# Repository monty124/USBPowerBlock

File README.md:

# USBPowerBlock
Tasmota controlled USB Switching

# Why?

So many things are usb powered but can not or are not able to be integrated easily within Home Assistant; or programable.

Want to turn something on or off automatically? you will need to buy [something else](https://www.aliexpress.com/w/wholesale-TZT-sinilink-USB.html?spm=a2g0o.productlist.search.0)! and it still needs a power source

Want it to be integrated into [Home Assistant](https://www.home-assistant.io/) and or control its [privacy](https://www.voanews.com/a/east-asia-pacific_voa-news-china_cybersecurity-experts-worried-chinese-firms-control-smart-devices/6209815.html)? good luck off the shelf, you may need to [flash it](https://templates.blakadder.com/sinilink_XY-WFUSB.html) (if its supported)

Want more than one device powered from a single power source, you will need a powered hub and multiple other devices, or multiple power sources, this effectively combines 5 [sinilinks'](https://www.aliexpress.com/w/wholesale-TZT-sinilink-USB.html?spm=a2g0o.productlist.search.0) into a single unit.

It has been designed to power a device up to 500mA with the listed BOM, but is flexible (see Options below)

500mA was chosen as a default, as a 5v 2.5A/3A powesupply is very common and affordable (you probably already have one!) and this was intended to switch very low current devices (think, lights, IoT devices, etc)

For more information on USB power draw:

https://en.wikipedia.org/wiki/USB_hardware#Allowable_current_draw

Note, this does not identify itself as a PD or Battery Charging (BC) Device! (yet), technically each port should be limited to 100mA in its current design, but taking some liberties here!

# BOM

[Bill Of Materials](./USBPowerBlock_BOM.csv)

|Reference            |Value                    |Datasheet                                                                                                              |Qty                                                      |Product_Link|
|---------------------|-------------------------|-----------------------------------------------------------------------------------------------------------------------|---------------------------------------------------------|------------|
|C1,C3,C4,C6          |0.1UF-0805-25V-_+80_-20%_|https://www.lcsc.com/datasheet/lcsc_datasheet_2304140030_TORCH-CT41G-0805-2X1-50V-0-1-F-K-N_C126469.pdf                |4                                                        |https://www.lcsc.com/product-detail/C126469.html|
|C2,C5                |10UF-0805-16V-10%        |https://www.lcsc.com/datasheet/lcsc_datasheet_2409292003_Vishay-Intertech-VJ0805G106KXYTW1BC_C5334346.pdf              |2                                                        |https://www.lcsc.com/product-detail/C5334346.html|
|D1 |Blue |https://wmsc.lcsc.com/wmsc/upload/file/pdf/v2/lcsc/2208221800_TCWIN-TC0805GF01-1CSA_C5137315.pdf|1  |https://lcsc.com/product-detail/C5137315.html|
|D2 |Green|https://wmsc.lcsc.com/wmsc/upload/file/pdf/v2/lcsc/2410121920_Lite-On-LTST-C170KGKT_C98221.pdf  |1  |https://lcsc.com/product-detail/C5137315.html|
|D3 |Red  |https://wmsc.lcsc.com/wmsc/upload/file/pdf/v2/lcsc/2504101957_XINGLIGHT-XL-2012SURC_C965812.pdf |1  |https://lcsc.com/product-detail/C5137315.html|
|F1,F2,F3,F4,F5       |JK-SMD0805-020-30V       |https://www.lcsc.com/datasheet/lcsc_datasheet_2007081813_Jinrui-Electronic-Materials-Co--JK-SMD0805-020-30V_C516070.pdf|5                                                        |https://www.lcsc.com/product-detail/C516070.html|
|J1,J2,J3,J4,J5       |USB_A                    | Vertical USB-A                                                                                                                      |5                                                        |https://www.aliexpress.com/item/1005005865561469.html or https://www.lcsc.com/product-detail/C456015.html|
|J6 |IO   |~                                         |1  |~                                                    |
|J7                   |Power_In                 | XH2.5                                                                                                                      |1                                                        |https://www.aliexpress.com/item/1005003137518807.html|
|Q1,Q2,Q3,Q4,Q5       |LMAK15N10                |https://www.lcsc.com/datasheet/lcsc_datasheet_2504180925_VBsemi-Elec-ME15N10-VB_C710010.pdf                            |5                                                        |https://www.lcsc.com/product-detail/C710010.html|
|R1,R3,R4,R5,R7,R9,R11,R15,R16|10KOHM-0805-1_10W-1%     |https://www.lcsc.com/datasheet/lcsc_datasheet_2410121912_TyoHM-RMC080510K5-N_C269724.pdf                               |9                                                        |https://www.lcsc.com/product-detail/C269724.html|
|R2,R6,R8,R10,R12     |100R                     |https://www.lcsc.com/datasheet/lcsc_datasheet_2411221126_UNI-ROYAL-Uniroyal-Elec-0805W8F1000T5E_C17408.pdf             |5                                                        |https://www.lcsc.com/product-detail/C17408.html|
|R13,R17|68OHM-0805-1_10W-1%|https://www.lcsc.com/datasheet/lcsc_datasheet_2410121912_TyoHM-RMC080510K5-N_C269724.pdf|2  |https://www.lcsc.com/product-detail/C269724.html|
|R14    |470OHM-0805-1_10W-1%|https://www.lcsc.com/datasheet/lcsc_datasheet_2410121912_TyoHM-RMC080510K5-N_C269724.pdf|1  |https://www.lcsc.com/product-detail/C269724.html|
|U1                   |ESP-WROOM-02             |https://www.espressif.com/sites/default/files/documentation/0c-esp-wroom-02_datasheet_en.pdf                           |1                                                        |https://www.lcsc.com/product-detail/C529584.html|
|U2                   |AMS1117-3.3              |http://www.advanced-monolithic.com/pdf/ds1117.pdf                                                                      |1                                                        |https://www.lcsc.com/product-detail/C2992570.html|

Misc Components:

| Product | Example Link | Qty |
| ------- | -------------| --- |
| 5V 2.5A (min) Power Supply | https://www.wagneronline.com.au/5-volt-3a-switch-mode/power-supplies/power-lighting/smp5v-3a-21r-35234/10297/pd/ | 1 |
| Power Socket 5.5x2.1mm| https://www.aliexpress.com/item/1005002601060281.html | 1 |
| Hook Up Wire ~24AWG | https://www.aliexpress.com/item/1005007278251470.html | 1x Length Red <br> 1x Length Black |
| PCB | [Here](./USBPowerBlock/gerber) | 1 |
| Case | [Here](./Case) | 1 |
| Flexy Pins | https://core-electronics.com.au/flexypin-pack-of-100.html | 18 |

# Options

## I want more current! 

- Swap out your power adaptor for something that can supply your desired current along with approx (at least) ~250mA for the ESP
- Replace F1-F5 with a suitable current rating; 0805 package self healing fuse

  - https://www.lcsc.com/product-detail/C516070.html 500mA
  - https://www.lcsc.com/product-detail/C369151.html 1.5A
  - https://www.lcsc.com/product-detail/C2830234.html 2.2A
  
The MOSFETS are rated to approx 15A each, which is overkill.

## I don't need switched outputs but want like 5 powered USB ports

- leave all components out except J1-J5 + J7
- leave F1-F5 in (and up-rate the fuse value, see above) or replace with 0805 0 Ohm links (https://www.lcsc.com/product-detail/C96345.html)
- solder JP1-JP5
- ensure your power adaptor has enough current

# PCB

Gerber files are available to have printed

- https://www.pcbway.com/
- https://jlcpcb.com/

# 3D Printed Case

STL's are available in this repo to print or have printed

- https://www.pcbway.com/rapid-prototyping/manufacture/?type=2
- https://jlc3dp.com/?source=JLCPCB-top-productbar

# Assembly

TBC

# Tasmota

TBC

# What Next?

Some notes on desired features! (maybe, but probably not)

- Power from a 12V supply?
- Increased power outputs and PD/BC support?
- Compliant USB-C PD Power Source 
- Completed photos
- Flexypin-less design?
- ESP32-C3-WROOM design (ESP-WROOM-02 is EOL) with and without FlexyPin

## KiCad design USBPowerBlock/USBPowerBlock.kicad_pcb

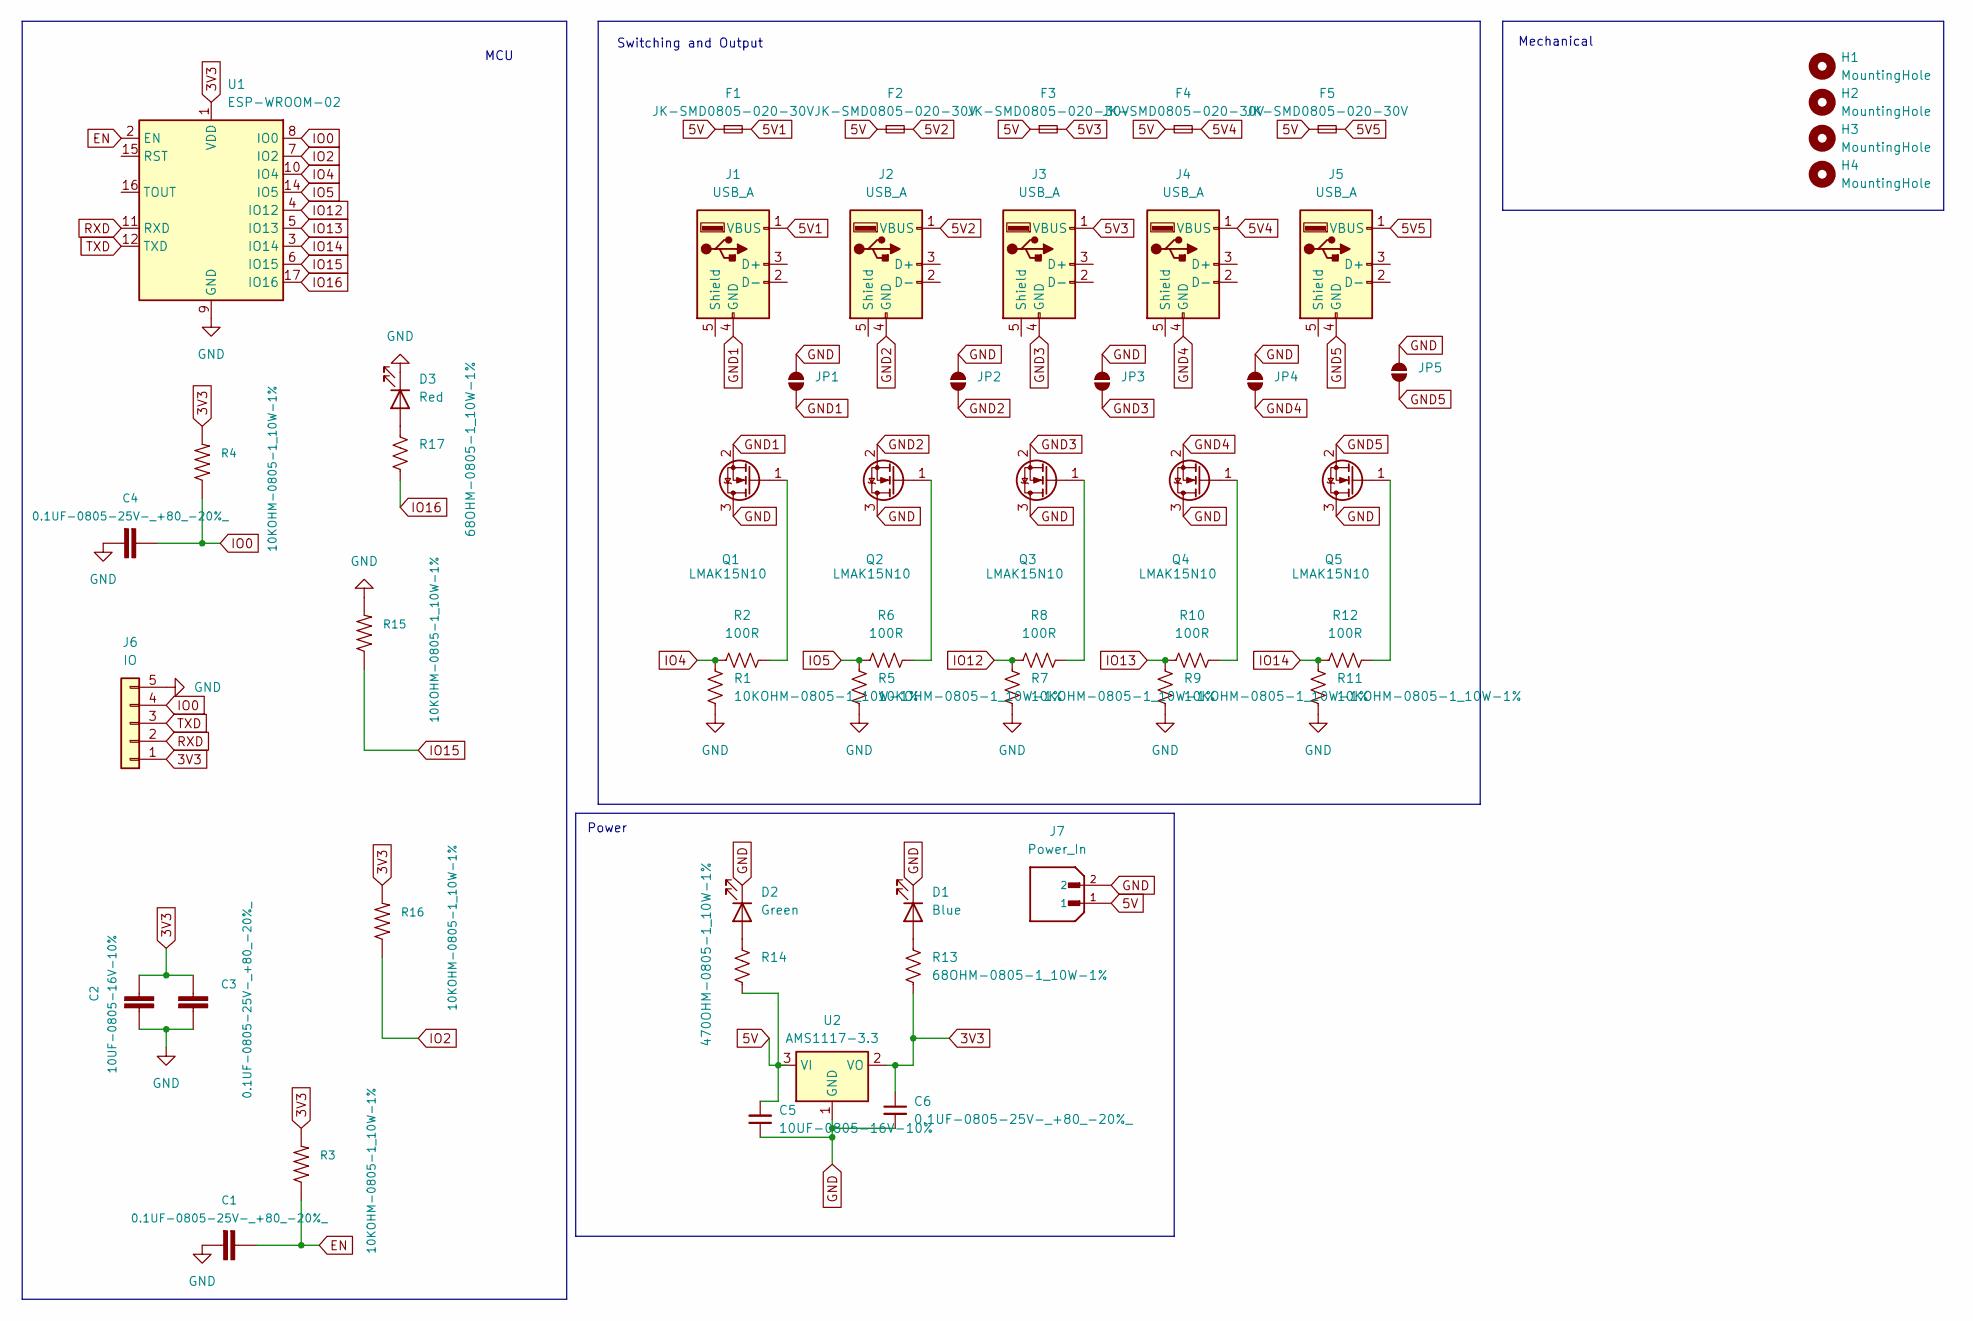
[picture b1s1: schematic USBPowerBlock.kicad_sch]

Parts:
C1, C3, C4, C6: 0.1UF-0805-25V-_+80_-20%_; C_0805_2012Metric_Pad1.18x1.45mm_HandSolder
C2, C5: 10UF-0805-16V-10%; C_0805_2012Metric_Pad1.18x1.45mm_HandSolder
D1: Blue; LED_0805_2012Metric_Pad1.15x1.40mm_HandSolder
D2: Green; LED_0805_2012Metric_Pad1.15x1.40mm_HandSolder
D3: Red; LED_0805_2012Metric_Pad1.15x1.40mm_HandSolder
F1, F2, F3, F4, F5: JK-SMD0805-020-30V; Fuse_0805_2012Metric_Pad1.15x1.40mm_HandSolder
H1, H2, H3, H4: MountingHole; MountingHole_3.2mm_M3
J1, J2, J3, J4, J5: USB_A; USB_11_Aliexpress
J6: IO; PinHeader_1x05_P1.27mm_Vertical
J7: Power_In; JST_B2B-XH-A; PARTREV N/A
JP1, JP2, JP3, JP4, JP5: SMT-JUMPER_2_NO_SILK
Q1, Q2, Q3, Q4, Q5: LMAK15N10; TO-252-2
R1, R3, R4, R5, R7, R9, R11, R15, R16: 10KOHM-0805-1_10W-1%; R_0805_2012Metric_Pad1.20x1.40mm_HandSolder
R2, R6, R8, R10, R12: 100R; R_0805_2012Metric_Pad1.20x1.40mm_HandSolder
R13, R17: 68OHM-0805-1_10W-1%; R_0805_2012Metric_Pad1.20x1.40mm_HandSolder
R14: 470OHM-0805-1_10W-1%; R_0805_2012Metric_Pad1.20x1.40mm_HandSolder
U1: ESP-WROOM-02; ESP-WROOM-02-Flexy
U2: AMS1117-3.3; SOT-223-3_TabPin2

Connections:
3V3: C2.1, C3.1, C6.1, J6.1, R3.2, R4.2, R13.1, R16.2, U1.1 (VDD), U2.2 (VO)
5V: C5.2, F1.1, F2.1, F3.1, F4.1, F5.1, J7.1, R14.1, U2.3 (VI)
5V1: F1.2, J1.1 (VBUS)
5V2: F2.2, J2.1 (VBUS)
5V3: F3.2, J3.1 (VBUS)
5V4: F4.2, J4.1 (VBUS)
5V5: F5.2, J5.1 (VBUS)
EN: C1.1, R3.1, U1.2 (EN)
GND: C1.2, C2.2, C3.2, C4.2, C5.1, C6.2, D1.1 (K), D2.1 (K), D3.1 (K), J6.5, J7.2, JP1.2 (B), JP2.2 (B), JP3.2 (B), JP4.2 (B), JP5.2 (B), Q1.3 (D), Q2.3 (D), Q3.3 (D), Q4.3 (D), Q5.3 (D), R1.1, R5.1, R7.1, R9.1, R11.1, R15.2, U1.9 (GND), U1.13 (GND), U1.18 (GND), U1.19 (GND), U2.1 (GND)
GND1: J1.4 (GND), JP1.1 (A), Q1.2 (S)
GND2: J2.4 (GND), JP2.1 (A), Q2.2 (S)
GND3: J3.4 (GND), JP3.1 (A), Q3.2 (S)
GND4: J4.4 (GND), JP4.1 (A), Q4.2 (S)
GND5: J5.4 (GND), JP5.1 (A), Q5.2 (S)
IO0: C4.1, J6.4, R4.1, U1.8 (IO0)
IO2: R16.1, U1.7 (IO2)
IO4: R1.2, R2.1, U1.10 (IO4)
IO5: R5.2, R6.1, U1.14 (IO5)
IO12: R7.2, R8.1, U1.4 (IO12)
IO13: R9.2, R10.1, U1.5 (IO13)
IO14: R11.2, R12.1, U1.3 (IO14)
IO15: R15.1, U1.6 (IO15)
IO16: R17.1, U1.17 (IO16)
unnamed: D1.2 (A), R13.2
unnamed: D2.2 (A), R14.2
unnamed: D3.2 (A), R17.2
unnamed: Q1.1 (G), R2.2
unnamed: Q2.1 (G), R6.2
unnamed: Q3.1 (G), R8.2
unnamed: Q4.1 (G), R10.2
unnamed: Q5.1 (G), R12.2
RXD: J6.2, U1.11 (RXD)
TXD: J6.3, U1.12 (TXD)

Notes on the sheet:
Mechanical
Power
MCU
Switching and Output

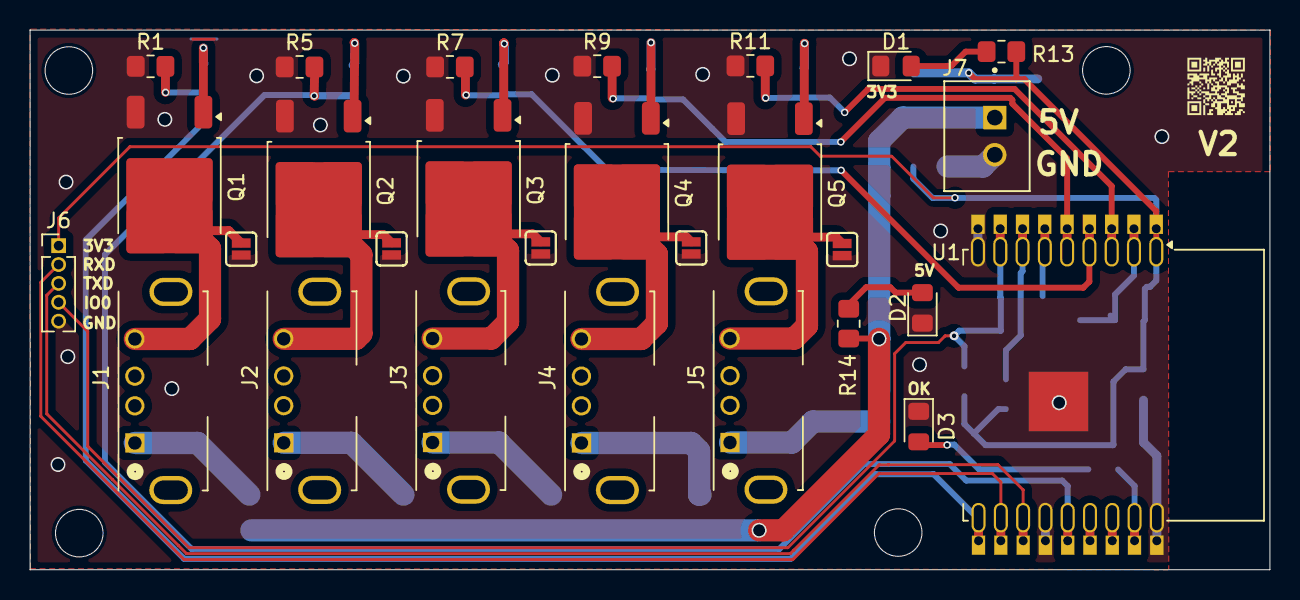
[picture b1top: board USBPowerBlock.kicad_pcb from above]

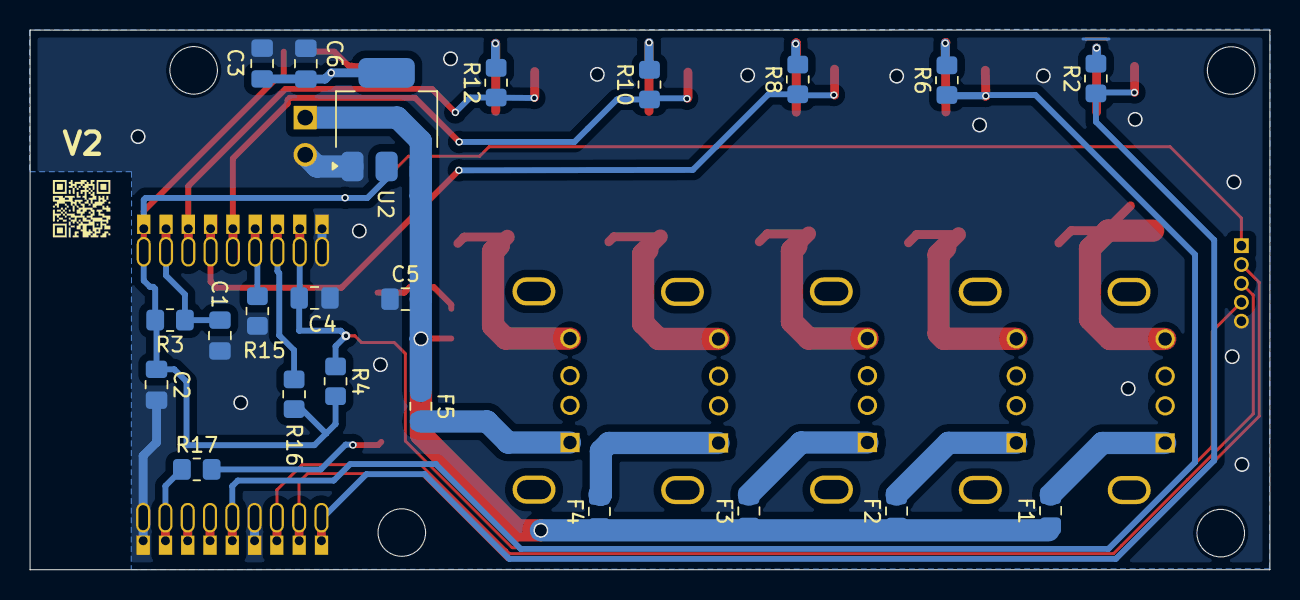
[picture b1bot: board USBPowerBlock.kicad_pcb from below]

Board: 2 copper layers, 83.5 x 36.3 mm, 54 parts (22 on the bottom side), 33 nets.

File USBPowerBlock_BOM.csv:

"Reference","Value","Datasheet","Qty","Product_Link"
"C1,C3,C4,C6","0.1UF-0805-25V-_+80_-20%_","https://www.lcsc.com/datasheet/lcsc_datasheet_2304140030_TOR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","4","https://www.lcsc.com/product-detail/C126469.html"
"C2,C5","10UF-0805-16V-10%","https://www.lcsc.com/datasheet/lcsc_datasheet_2409292003_Vis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","2","https://www.lcsc.com/product-detail/C5334346.html"
"D1","Blue","https://wmsc.lcsc.com/wmsc/upload/file/pdf/v2/lcsc/220822180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","1","https://lcsc.com/product-detail/C5137315.html"
"D2","Green","https://wmsc.lcsc.com/wmsc/upload/file/pdf/v2/lcsc/241012192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","1","https://lcsc.com/product-detail/C5137315.html"
"D3","Red","https://wmsc.lcsc.com/wmsc/upload/file/pdf/v2/lcsc/250410195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","1","https://lcsc.com/product-detail/C5137315.html"
"F1,F2,F3,F4,F5","JK-SMD0805-020-30V","https://www.lcsc.com/datasheet/lcsc_datasheet_2007081813_Jin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","5","https://www.lcsc.com/product-detail/C516070.html"
"J1,J2,J3,J4,J5","USB_A","~","5","https://www.aliexpress.com/item/1005005865561469.html or https://www.lcsc.com/product-detail/C456015.html"
"J6","IO","~","1","~"
"J7","Power_In","~","1","https://www.aliexpress.com/item/1005003137518807.html"
"JP1,JP2,JP3,JP4,JP5","~","~","5","~"
"Q1,Q2,Q3,Q4,Q5","LMAK15N10","https://www.lcsc.com/datasheet/lcsc_datasheet_2504180925_VBs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","5","https://www.lcsc.com/product-detail/C710010.html"
"R1,R3,R4,R5,R7,R9,R11,R15,R16","10KOHM-0805-1_10W-1%","https://www.lcsc.com/datasheet/lcsc_datasheet_2410121912_Tyo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","9","https://www.lcsc.com/product-detail/C269724.html"
"R2,R6,R8,R10,R12","100R","https://www.lcsc.com/datasheet/lcsc_datasheet_2411221126_UNI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","5","https://www.lcsc.com/product-detail/C17408.html"
"R13,R17","68OHM-0805-1_10W-1%","https://www.lcsc.com/datasheet/lcsc_datasheet_2410121912_Tyo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","2","https://www.lcsc.com/product-detail/C269724.html"
"R14","470OHM-0805-1_10W-1%","https://www.lcsc.com/datasheet/lcsc_datasheet_2410121912_Tyo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","1","https://www.lcsc.com/product-detail/C269724.html"
"U1","ESP-WROOM-02","https://www.espressif.com/sites/default/files/documentation/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","1","https://www.lcsc.com/product-detail/C529584.html"
"U2","AMS1117-3.3","http://www.advanced-monolithic.com/pdf/ds1117.pdf","1","https://www.lcsc.com/product-detail/C2992570.html"

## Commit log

2025-06-22 initial commit - v1
    initial commit for version 1
2025-10-26 V2
    Fix for V2 stuff up and Assembly Photos
